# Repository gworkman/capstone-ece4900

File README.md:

# Capstone Project
This is the Capstone project for Team 7 at The Ohio State University Department of Electrical and Computer Engineering

# Software
This project includes a websocket server, written in Python3, that exposes the sensor data that was read over Bluetooth to another process. it also includes an example client, which is a webpage that uses a websocket and charts.js to plot the received data in real time. 

## Server
The server is a very basic implementation, provided as a proof of concept. The server starts a websocket server, which waits for connections on localhost port 8888. When it receives a connection, is starts scanning for Bluetooth devices, and connects to the ESP32 device. After connecting, it starts streaming the received accelerometer, gyroscope, and force sensor readings to the connected websocket client. If additional sensors are added and supported by the firmware in the future, the values sent and received in the websocket server will need to be updated.

# Firmware
This project uses the ESP32 port of Micropython. The most recent firmware versions for the ESP32 are located in the firmware directory of the repository, along with the micropython firmware files

## Getting started
To get started developing with Micropython for this project, the following steps are required:
1. Install [Python](https://www.python.org/downloads/), if not already installed
2. Use pip to install [esptool](https://pypi.org/project/esptool/) and [adafruit-ampy](https://pypi.org/project/adafruit-ampy/) by running `pip install esptool adafruit-ampy`
3. Ensure the `make` utility is installed (for Windows users, see WSL)

The following tools are highly recommended:
1. [VS Code](https://code.visualstudio.com), with the python extension installed
2. A serial port monitor, such as the one included with the [Arduino IDE](https://www.arduino.cc/en/Main/Software), the GNU utility `screen`, or the terminal emulator program [PuTTY](https://www.chiark.greenend.org.uk/~sgtatham/putty/latest.html)

### Flashing the firmware
To flash the firmware, run `make flash` in the root directory of the repository. This will flash the provided micropython firmware for the ESP32. There are two versions of the firmware, one compiled with the version 3 of the ESP-IDF toolchain and one compiled with version 4. The default option flashes the version 4 variant of the firmware.

This process can take a while.

### Working with micropython files on the ESP32
The below table shows the commands that can be run using the makefile to work with files on the ESP32. Most of the commands require the port as an argument to the command. The port that the ESP32 is attached to depends on what operating system you are running. To find the port on Mac, run `ls /dev/tty.*` in the terminal to get a list of currently attached serial ports. For windows, the port is a COM port, and can be found by opening the Device Manager and navigating to the ports list.

Command | Arguments | Description | Example
------- | --------- | ----------- | -------
`make flash` | `port` | Flashes the micropython firmware to the ESP32 | `make flash port=/dev/tty.usbserieal-14120`
`make list` | `port` | Lists the files currently on the ESP32 | `make list port=/dev/tty.usbserial-14120`
`make put` | `port`, `file` | Loads a file from the local filesystem to the ESP32's internal filesystem | `make put port=/dev/tty.usbserial-14120 file=software/src/boot.py`
`make show` | `port`, `file` | Gets and prints out the contents of a file currently on the ESP32 | `make show port=/dev/tty.usbserial-14120 file=main.py`
`make reset` | `port` | Performs a hard reset of the ESP32 | `make reset port=/dev/tty.usbserial-14120`

To get a running demo of the latest code in the repository, each of the micropython files in the [firmware](https://github.com/gworkman/capstone-ece4900/tree/master/firmware) directory should be loaded using the `make put` command shown above.

### Overview
The following is a brief description of each of the files in the micropython firmware.

`boot.py`: This file is executed once on power reset. It simply turns of the ESP32 debugging, which clutters the serial port output.

`main.py`: This is where all of the business logic of the application occurs. This file is responsible for registering Bluetooth services, accepting Bluetooth connections, reading the sensor values, sending data packets, and the sleep modes. Most of the required future changes to this application will occur here.

`ble_advertising.py`: This file contains helper functions to create Bluetooth advertising payloads that are broadcast while the device is waiting for a connection. It specifies the name of the device, services that is has, and more. 

`imu.py`: This file has the logic for reading sensor data for the MPU6050. This file was referenced from the micropython MPU9x50 library, found [here](https://github.com/micropython-IMU/micropython-mpu9x50).

`vector3d.py`: This file is required by `imu.py`, and is a generalized abstraction of the three-axis sensor data values, particularly the gyroscope and accelerometer data.

# Hardware
This project includes a custom-designed add-on board for the ESP32 to mount a variety of sensors in a small package.

## Getting started
If you just want to purchase the board, you can use the gerber files in the `hardware/output.zip` file. A bill of materials and PDF of the schematic is also included in the hardware/output directory for reference.
To make changes to the design of the board, you will need KiCad, a free PCB design software. Just open the `hardware.pro` file in KiCad, then you are good to start making changes. If the schematic doens't load in some of the symbols correctly, you might need to update the library paths to point to the `hardware/libraries` folder for the project.

## Overview
The schematic includes several components. First is the ESP32 microcontroller, which suppies the power and ground for the rest of the circuit. This component has connections to read data from and control other parts of the circuit.

Second, the MPU6050 contains all of the circuitry to ensure that this accelerometer/gyro chip works as expected. It has connections to the ESP32 in the form of I2C SDA and SCL lines, as well as a configurable interrupt line. 

Third, the capacitive presence sensor chip, the FDC2212, has the circuitry that sets the correct sensor oscillation frequency, as described in the datasheet. However, it also requires a capacitive plate to work effectively, which can be externally mounted by soldering a wire to the capacitive plate and the soldering point. The chip has inputs and outputs to the microcontroller via the I2C SDA and SCL lines, as well as an interrupt and reset line.

Next, the acoustic time of flight sensor block is comprised of a connector and a 1.8v voltage regulator. The development board that the chip is mounted to has all of the required circuitry, it simply requires 1.8v and a connector and ribbon cable to be able to correctly operate.

Finally, the force-sensitive resistor is a relatively simply circuit. It uses a voltage divider circuit to vary the output voltage with the pressure applied to the force sensor. The analog voltage is read by the microcontroller's ADC.

## Notes
One thing to keep in mind while changing the board layout design is the position of the decoupling capacitors. These should generally be placed as close to the power supply pins of each of the chips as possible, which helps to reduce noise and get accurate readings from the sensors.

There are several extra IO pins that are exposed to allow for expansions of the board to other features. IO pin 12 is currently used in the prototype of the firmware as a reset button. This feature is configurable in the firmware.

Finally, some of the pins on the ESP32 can only be used as inputs. These pins are labelled in a note within the schematic.

## Rendering
The below image is a rendering of the final design of the hardware for this project. The rendering shows almost all of the passive components on the board, with most of the chips. It does not include the connector for the acoustics sensor (bottom right) or the ESP32 development board (which is shown with the outline). It includes mounting holes in each of the corners for securely fastening the device.

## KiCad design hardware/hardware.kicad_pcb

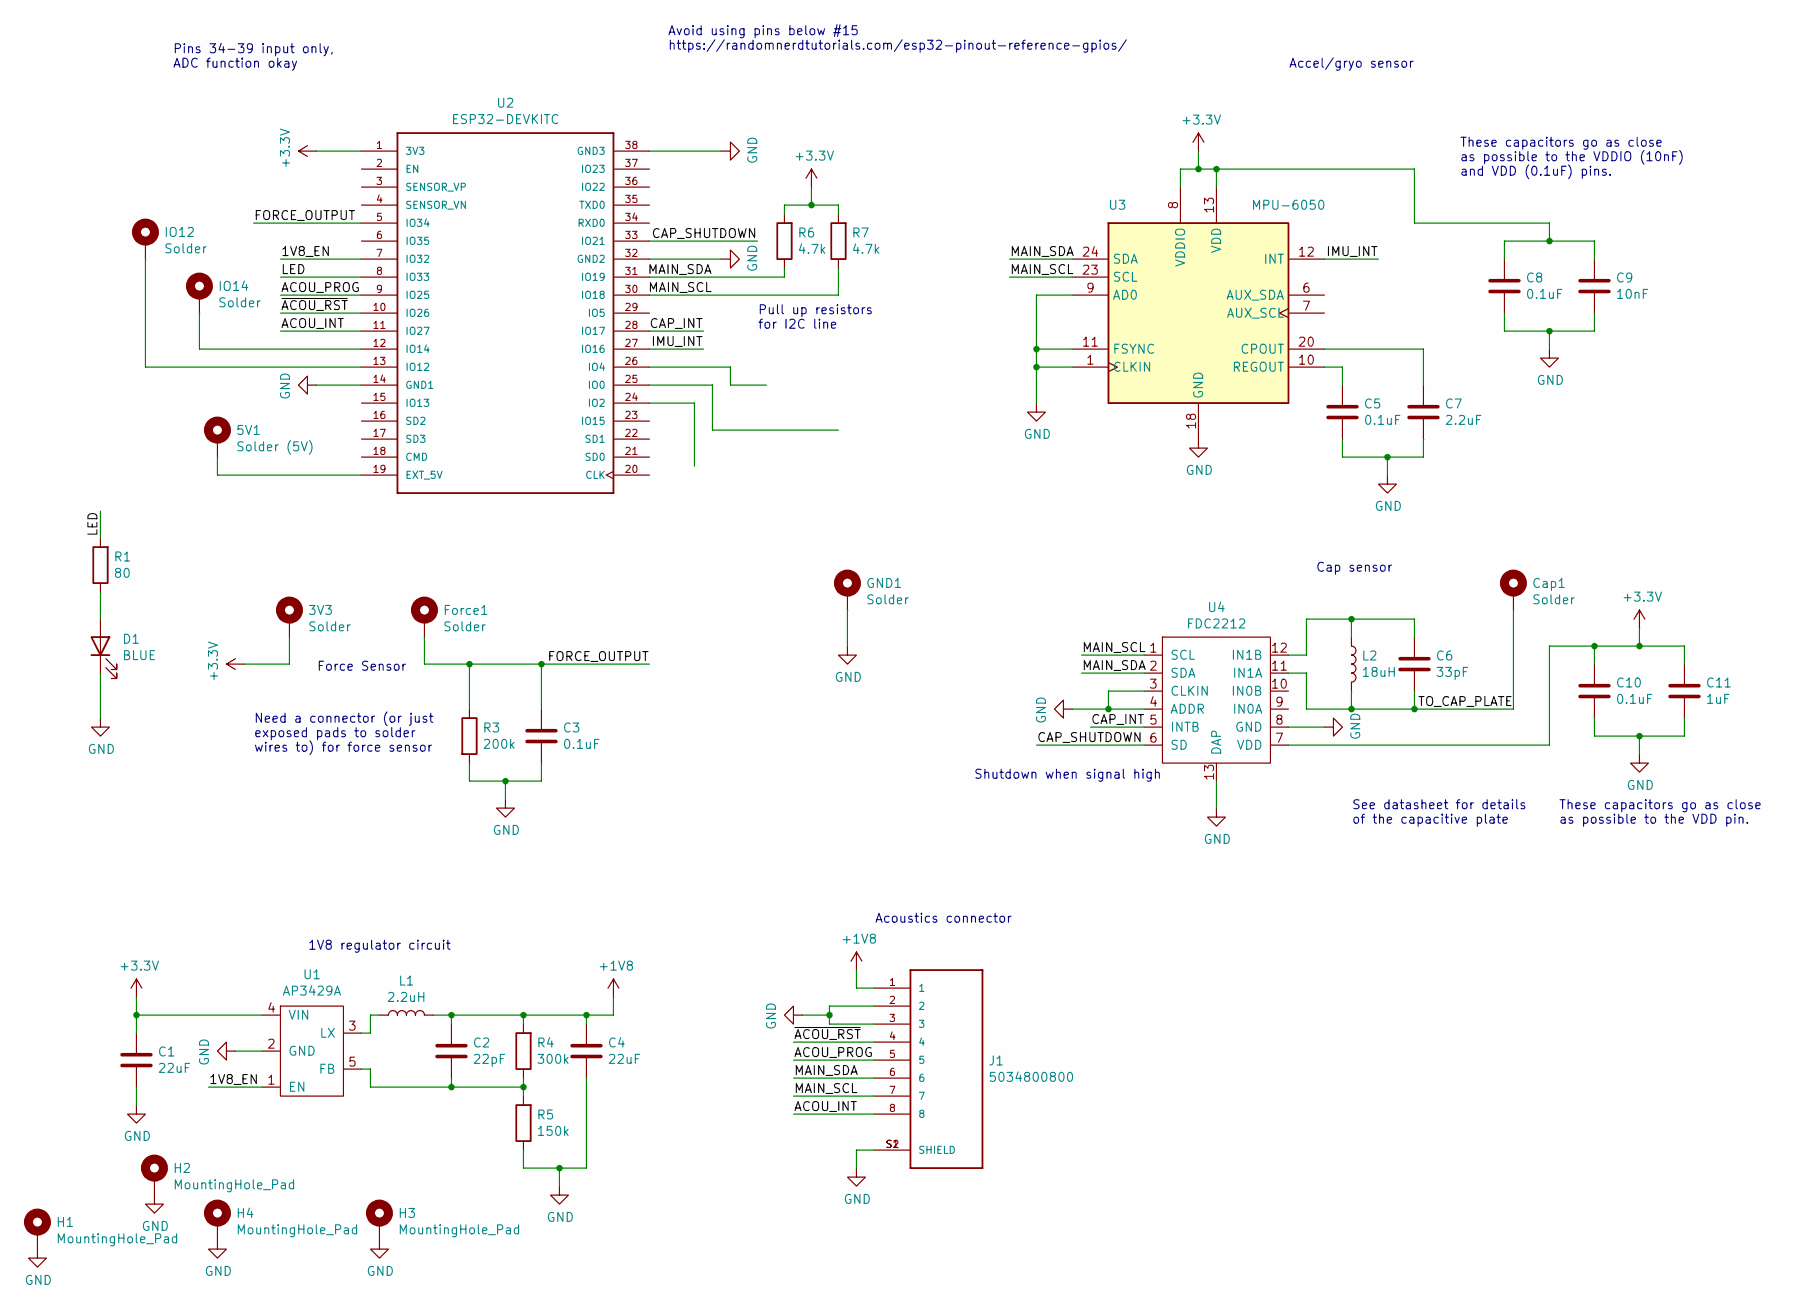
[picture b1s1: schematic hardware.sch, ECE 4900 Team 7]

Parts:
3V3: Solder; MountingHole_2.2mm_M2_ISO14580_Pad
5V1: Solder (5V); MountingHole_2.2mm_M2_ISO14580_Pad
C1, C4: 22uF; C_0603_1608Metric_Pad1.05x0.95mm_HandSolder
C2: 22pF; C_0603_1608Metric_Pad1.05x0.95mm_HandSolder
C3, C5, C8, C10: 0.1uF; C_0603_1608Metric_Pad1.05x0.95mm_HandSolder
C6: 33pF; C_0603_1608Metric_Pad1.05x0.95mm_HandSolder
C7: 2.2uF; C_0603_1608Metric_Pad1.05x0.95mm_HandSolder
C9: 10nF; C_0603_1608Metric_Pad1.05x0.95mm_HandSolder
C11: 1uF; C_0603_1608Metric_Pad1.05x0.95mm_HandSolder
Cap1: Solder; MountingHole_2.2mm_M2_ISO14580_Pad
D1: BLUE; LED_0603_1608Metric_Pad1.05x0.95mm_HandSolder
Force1: Solder; MountingHole_2.2mm_M2_ISO14580_Pad
GND1: Solder; MountingHole_2.2mm_M2_ISO14580_Pad
H1, H2, H3, H4: MountingHole_Pad; MountingHole_3.2mm_M3_Pad
IO12, IO14: Solder; MountingHole_2.2mm_M2_ISO14580_Pad
J1: 5034800800; MOLEX_5034800800
L1: 2.2uH; L_0603_1608Metric_Pad1.05x0.95mm_HandSolder
L2: 18uH; L_0603_1608Metric_Pad1.05x0.95mm_HandSolder
R1: 80; R_1206_3216Metric
R3: 200k; R_0603_1608Metric_Pad1.05x0.95mm_HandSolder
R4: 300k; R_0603_1608Metric_Pad1.05x0.95mm_HandSolder
R5: 150k; R_0603_1608Metric_Pad1.05x0.95mm_HandSolder
R6, R7: 4.7k; R_0603_1608Metric_Pad1.05x0.95mm_HandSolder
U1: AP3429A; TSOT25
U2: ESP32-DEVKITC; MODULE_ESP32-DEVKITC
U3: MPU-6050; InvenSense_QFN-24_4x4mm_P0.5mm
U4: FDC2212; WSON-12-1EP_4x4mm_P0.5mm_EP2.6x3mm

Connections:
+1V8: C2.1, C4.1, J1.1, L1.2, R4.2
+3V3: 3V3.1, C1.1, C8.2, C9.2, C10.2, C11.2, R6.2, R7.2, U1.4 (VIN), U2.1 (3V3), U3.8 (VDDIO), U3.13 (VDD), U4.7 (VDD)
/1V8_EN: U1.1 (EN), U2.7 (IO32)
/ACOU_INT: J1.8, U2.11 (IO27)
/ACOU_PROG: J1.5, U2.9 (IO25)
/CAP_INT: U2.28 (IO17), U4.5 (INTB)
/CAP_SHUTDOWN: U2.33 (IO21), U4.6 (SD)
/FORCE_OUTPUT: C3.2, Force1.1, R3.1, U2.5 (IO34)
/IMU_INT: U2.27 (IO16), U3.12 (INT)
/LED: R1.2, U2.8 (IO33)
/MAIN_SCL: J1.7, R7.1, U2.30 (IO18), U3.23 (SCL), U4.1 (SCL)
/MAIN_SDA: J1.6, R6.1, U2.31 (IO19), U3.24 (SDA), U4.2 (SDA)
/TO_CAP_PLATE: C6.2, Cap1.1, L2.2, U4.11 (IN1A)
/~ACOU_RST: J1.4, U2.10 (IO26)
GND: C1.2, C3.1, C4.2, C5.2, C7.2, C8.1, C9.1, C10.1, C11.1, D1.1 (K), GND1.1, H1.1, H2.1, H3.1, H4.1, J1.2, J1.3, J1.S1 (SHIELD), J1.S2 (SHIELD), R3.2, R5.1, U1.2 (GND), U2.14 (GND1), U2.32 (GND2), U2.38 (GND3), U3.1 (CLKIN), U3.9 (AD0), U3.11 (FSYNC), U3.18 (GND), U4.3 (CLKIN), U4.4 (ADDR), U4.8 (GND), U4.13 (DAP)
unnamed: 5V1.1, U2.19 (EXT_5V)
unnamed: C2.2, R4.1, R5.2, U1.5 (FB)
unnamed: C5.1, U3.10 (REGOUT)
unnamed: C6.1, L2.1, U4.12 (IN1B)
unnamed: C7.1, U3.20 (CPOUT)
unnamed: D1.2 (A), R1.1
unnamed: IO12.1, U2.13 (IO12)
unnamed: IO14.1, U2.12 (IO14)
unnamed: L1.1, U1.3 (LX)

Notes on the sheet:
These capacitors go as close as possible to the VDDIO (10nF) and VDD (0.1uF) pins.
Pull up resistors for I2C line
These capacitors go as close as possible to the VDD pin.
Shutdown when signal high
1V8 regulator circuit
Acoustics connector
Accel/gryo sensor
Cap sensor
Need a connector (or just exposed pads to solder wires to) for force sensor
Force Sensor
Pins 34-39 input only, ADC function okay
Avoid using pins below #15 https://randomnerdtutorials.com/esp32-pinout-reference-gpios/
See datasheet for details of the capacitive plate

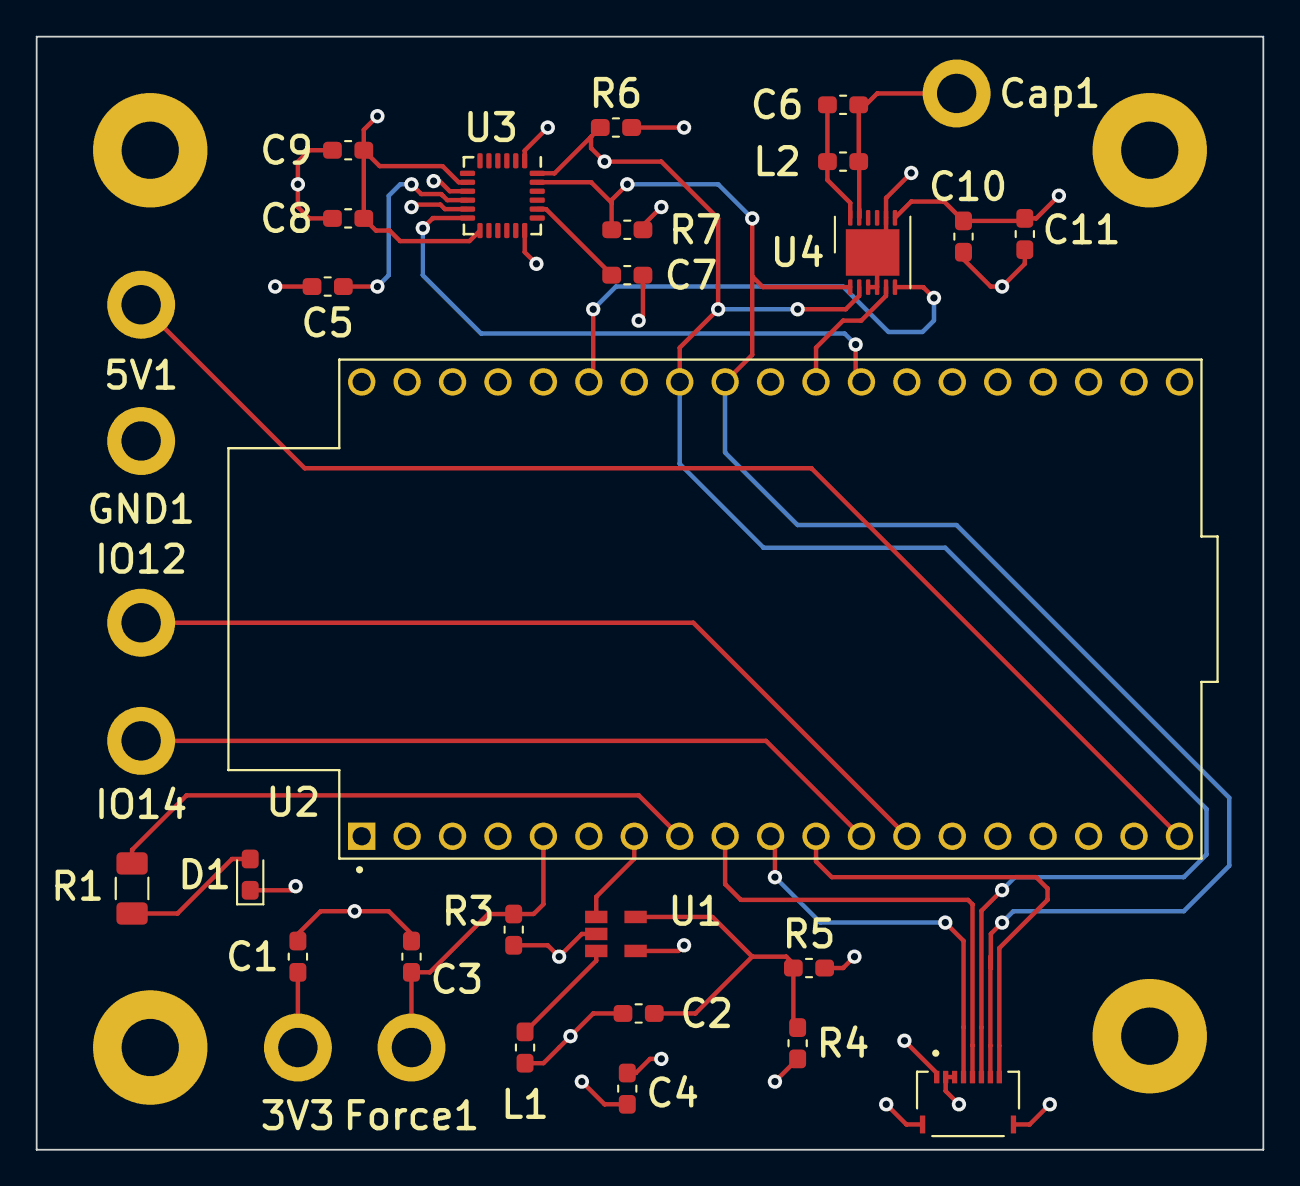
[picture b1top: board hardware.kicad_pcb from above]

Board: 4 copper layers, 68.6 x 62.2 mm, 36 parts (0 on the bottom side), 24 nets.

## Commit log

2020-09-24 create kicad project
2020-10-14 add micropython vs code setup
2020-10-14 add esp32 and mpu6050 to schematic
2020-10-15 prepare working demo
2020-10-15 add simulation mode
2020-10-19 add cap sensor to schematic
2020-10-20 add acoustic and force sensor in schematic
2020-10-20 initial draft of schematic
2020-10-22 PCB Update 10/22
2020-10-26 PCB Changes 10/25
2020-10-26 PCB 10/25
2020-10-28 IO Output
2020-10-29 GND Plane - New
2020-11-15 Added sleep wakeup from a pin
2020-12-02 Button sleeps esp32 now as well
2020-12-02 added gyro and force characteristics
2020-12-02 fixed bug in notify code
2020-12-02 advertise after disconnect
2020-12-02 add html graphing and socket server
2020-12-02 fix the server
2020-12-07 restructure files
2020-12-07 update readme and add output zip file
2020-12-07 include render in readme
